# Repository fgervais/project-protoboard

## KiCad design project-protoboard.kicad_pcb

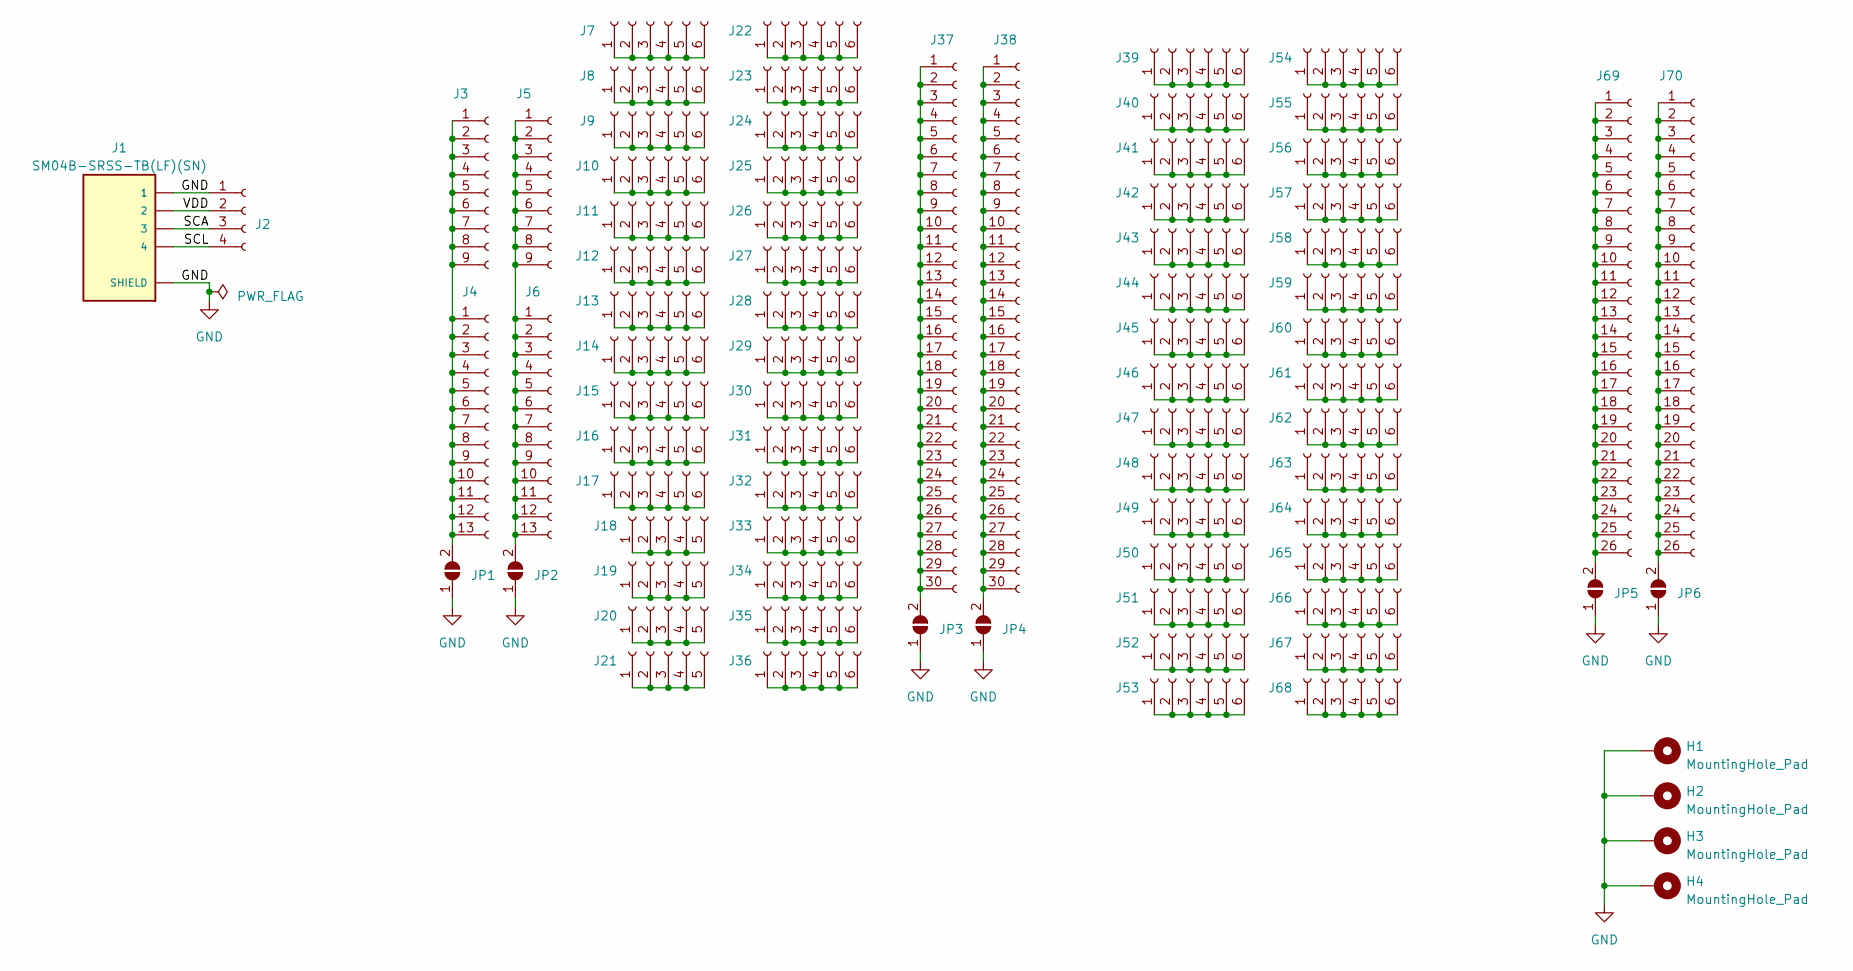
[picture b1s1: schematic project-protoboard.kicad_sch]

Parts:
H1, H2, H3, H4: MountingHole_Pad; MountingHole_2.7mm_M2.5_ISO7380_Pad
J1: SM04B-SRSS-TB(LF)(SN); JST_SM04B-SRSS-TB(LF)(SN)
J2: Conn_01x04_Socket; Proto_1x04_P2.54mm
J3, J5: Conn_01x09_Socket; Proto_1x09_P2.54mm
J4, J6: Conn_01x13_Socket; Proto_1x13_P2.54mm
J7, J8, J9, J10, J11, J12, J13, J14, J15, J16, J17, J22, J23, J24, J25, J26, J27, J28, J29, J30, J31, J32, J33, J34, J35, J36, J39, J40, J41, J42, J43, J44, J45, J46, J47, J48, J49, J50, J51, J52, J53, J54, J55, J56, J57, J58, J59, J60, J61, J62, J63, J64, J65, J66, J67, J68: Conn_01x06_Socket; Proto_1x06_P2.54mm
J18, J19, J20, J21: Conn_01x05_Socket; Proto_1x05_P2.54mm
J37, J38: Conn_01x30_Socket; Proto_1x30_P2.54mm
J69, J70: Conn_01x26_Socket; Proto_1x26_P2.54mm
JP1, JP2, JP3, JP4, JP5, JP6: SolderJumper_2_Open; SolderJumper-2_P1.3mm_Open_RoundedPad1.0x1.5mm

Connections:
/SCA: J1.3, J2.3
/SCL: J1.4, J2.4
/VDD: J1.2, J2.2
GND: H1.1, H2.1, H3.1, H4.1, J1.1, J1.S1 (SHIELD), J1.S2 (SHIELD), J2.1, JP1.1 (A), JP2.1 (A), JP3.1 (A), JP4.1 (A), JP5.1 (A), JP6.1 (A)
unnamed: J3.1, J3.2, J3.3, J3.4, J3.5, J3.6, J3.7, J3.8, J3.9, J4.1, J4.2, J4.3, J4.4, J4.5, J4.6, J4.7, J4.8, J4.9, J4.10, J4.11, J4.12, J4.13, JP1.2 (B)
unnamed: J5.1, J5.2, J5.3, J5.4, J5.5, J5.6, J5.7, J5.8, J5.9, J6.1, J6.2, J6.3, J6.4, J6.5, J6.6, J6.7, J6.8, J6.9, J6.10, J6.11, J6.12, J6.13, JP2.2 (B)
unnamed: J7.1, J7.2, J7.3, J7.4, J7.5, J7.6
unnamed: J8.1, J8.2, J8.3, J8.4, J8.5, J8.6
unnamed: J9.1, J9.2, J9.3, J9.4, J9.5, J9.6
unnamed: J10.1, J10.2, J10.3, J10.4, J10.5, J10.6
unnamed: J11.1, J11.2, J11.3, J11.4, J11.5, J11.6
unnamed: J12.1, J12.2, J12.3, J12.4, J12.5, J12.6
unnamed: J13.1, J13.2, J13.3, J13.4, J13.5, J13.6
unnamed: J14.1, J14.2, J14.3, J14.4, J14.5, J14.6
unnamed: J15.1, J15.2, J15.3, J15.4, J15.5, J15.6
unnamed: J16.1, J16.2, J16.3, J16.4, J16.5, J16.6
unnamed: J17.1, J17.2, J17.3, J17.4, J17.5, J17.6
unnamed: J18.1, J18.2, J18.3, J18.4, J18.5
unnamed: J19.1, J19.2, J19.3, J19.4, J19.5
unnamed: J20.1, J20.2, J20.3, J20.4, J20.5
unnamed: J21.1, J21.2, J21.3, J21.4, J21.5
unnamed: J22.1, J22.2, J22.3, J22.4, J22.5, J22.6
unnamed: J23.1, J23.2, J23.3, J23.4, J23.5, J23.6
unnamed: J24.1, J24.2, J24.3, J24.4, J24.5, J24.6
unnamed: J25.1, J25.2, J25.3, J25.4, J25.5, J25.6
unnamed: J26.1, J26.2, J26.3, J26.4, J26.5, J26.6
unnamed: J27.1, J27.2, J27.3, J27.4, J27.5, J27.6
unnamed: J28.1, J28.2, J28.3, J28.4, J28.5, J28.6
unnamed: J29.1, J29.2, J29.3, J29.4, J29.5, J29.6
unnamed: J30.1, J30.2, J30.3, J30.4, J30.5, J30.6
unnamed: J31.1, J31.2, J31.3, J31.4, J31.5, J31.6
unnamed: J32.1, J32.2, J32.3, J32.4, J32.5, J32.6
unnamed: J33.1, J33.2, J33.3, J33.4, J33.5, J33.6
unnamed: J34.1, J34.2, J34.3, J34.4, J34.5, J34.6
unnamed: J35.1, J35.2, J35.3, J35.4, J35.5, J35.6
unnamed: J36.1, J36.2, J36.3, J36.4, J36.5, J36.6
unnamed: J37.1, J37.2, J37.3, J37.4, J37.5, J37.6, J37.7, J37.8, J37.9, J37.10, J37.11, J37.12, J37.13, J37.14, J37.15, J37.16, J37.17, J37.18, J37.19, J37.20, J37.21, J37.22, J37.23, J37.24, J37.25, J37.26, J37.27, J37.28, J37.29, J37.30, JP3.2 (B)
unnamed: J38.1, J38.2, J38.3, J38.4, J38.5, J38.6, J38.7, J38.8, J38.9, J38.10, J38.11, J38.12, J38.13, J38.14, J38.15, J38.16, J38.17, J38.18, J38.19, J38.20, J38.21, J38.22, J38.23, J38.24, J38.25, J38.26, J38.27, J38.28, J38.29, J38.30, JP4.2 (B)
unnamed: J39.1, J39.2, J39.3, J39.4, J39.5, J39.6
unnamed: J40.1, J40.2, J40.3, J40.4, J40.5, J40.6
unnamed: J41.1, J41.2, J41.3, J41.4, J41.5, J41.6
unnamed: J42.1, J42.2, J42.3, J42.4, J42.5, J42.6
unnamed: J43.1, J43.2, J43.3, J43.4, J43.5, J43.6
unnamed: J44.1, J44.2, J44.3, J44.4, J44.5, J44.6
unnamed: J45.1, J45.2, J45.3, J45.4, J45.5, J45.6
unnamed: J46.1, J46.2, J46.3, J46.4, J46.5, J46.6
unnamed: J47.1, J47.2, J47.3, J47.4, J47.5, J47.6
unnamed: J48.1, J48.2, J48.3, J48.4, J48.5, J48.6
unnamed: J49.1, J49.2, J49.3, J49.4, J49.5, J49.6
unnamed: J50.1, J50.2, J50.3, J50.4, J50.5, J50.6
unnamed: J51.1, J51.2, J51.3, J51.4, J51.5, J51.6
unnamed: J52.1, J52.2, J52.3, J52.4, J52.5, J52.6
unnamed: J53.1, J53.2, J53.3, J53.4, J53.5, J53.6
unnamed: J54.1, J54.2, J54.3, J54.4, J54.5, J54.6
unnamed: J55.1, J55.2, J55.3, J55.4, J55.5, J55.6
unnamed: J56.1, J56.2, J56.3, J56.4, J56.5, J56.6
unnamed: J57.1, J57.2, J57.3, J57.4, J57.5, J57.6
unnamed: J58.1, J58.2, J58.3, J58.4, J58.5, J58.6
unnamed: J59.1, J59.2, J59.3, J59.4, J59.5, J59.6
unnamed: J60.1, J60.2, J60.3, J60.4, J60.5, J60.6
unnamed: J61.1, J61.2, J61.3, J61.4, J61.5, J61.6
unnamed: J62.1, J62.2, J62.3, J62.4, J62.5, J62.6
unnamed: J63.1, J63.2, J63.3, J63.4, J63.5, J63.6
unnamed: J64.1, J64.2, J64.3, J64.4, J64.5, J64.6
unnamed: J65.1, J65.2, J65.3, J65.4, J65.5, J65.6
unnamed: J66.1, J66.2, J66.3, J66.4, J66.5, J66.6
unnamed: J67.1, J67.2, J67.3, J67.4, J67.5, J67.6
unnamed: J68.1, J68.2, J68.3, J68.4, J68.5, J68.6
unnamed: J69.1, J69.2, J69.3, J69.4, J69.5, J69.6, J69.7, J69.8, J69.9, J69.10, J69.11, J69.12, J69.13, J69.14, J69.15, J69.16, J69.17, J69.18, J69.19, J69.20, J69.21, J69.22, J69.23, J69.24, J69.25, J69.26, JP5.2 (B)
unnamed: J70.1, J70.2, J70.3, J70.4, J70.5, J70.6, J70.7, J70.8, J70.9, J70.10, J70.11, J70.12, J70.13, J70.14, J70.15, J70.16, J70.17, J70.18, J70.19, J70.20, J70.21, J70.22, J70.23, J70.24, J70.25, J70.26, JP6.2 (B)

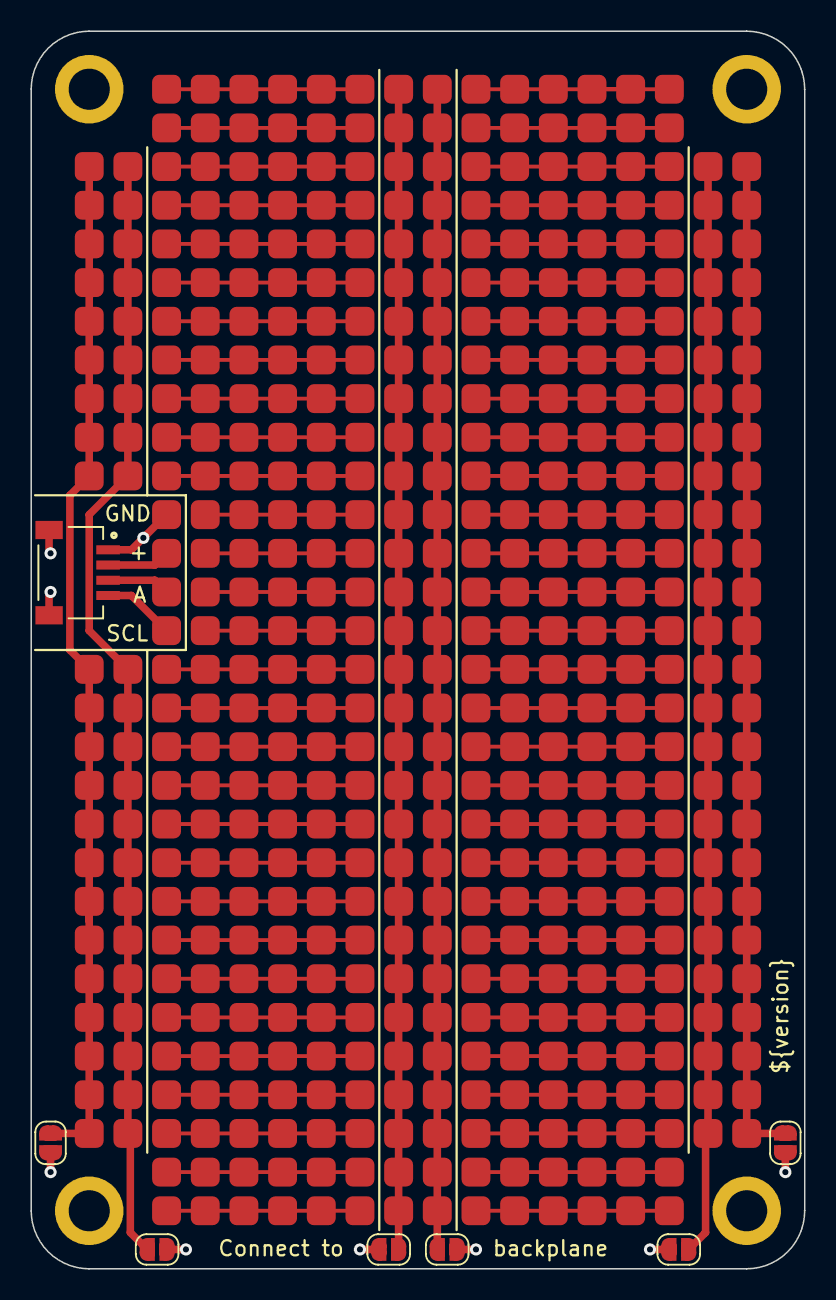
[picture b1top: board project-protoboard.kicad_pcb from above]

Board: 2 copper layers, 50.8 x 81.3 mm, 80 parts (0 on the bottom side), 70 nets.

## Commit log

2023-05-02 Update libraries to latest
2023-05-02 Blank kicad project
2023-05-03 Add one symbol of each
2023-05-03 Placement and board edge done
2023-05-04 First complete draft
2023-05-04 Add forgotten connection to ground
2023-05-05 change to project file
2023-05-05 Update library
2023-05-05 Add the `version` variable
2023-05-05 Add a version silkscreen
2023-05-05 Close pcbnew
2023-05-05 Update board version
2024-05-20 Add an overview image
2024-05-20 Add a close-up image
2025-08-24 Update gitignore
2025-08-24 Generate gerber files
